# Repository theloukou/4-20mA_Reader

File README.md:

# 4-20mA_Reader
4-20mA to UART/I2C output

Atmega328/Arduino based device.  
Features selectable auto UART transmission, and I2C polling.

## DISCLAIMER  
Device has not been tested yet. Contact me if you make a board and are willing to test.

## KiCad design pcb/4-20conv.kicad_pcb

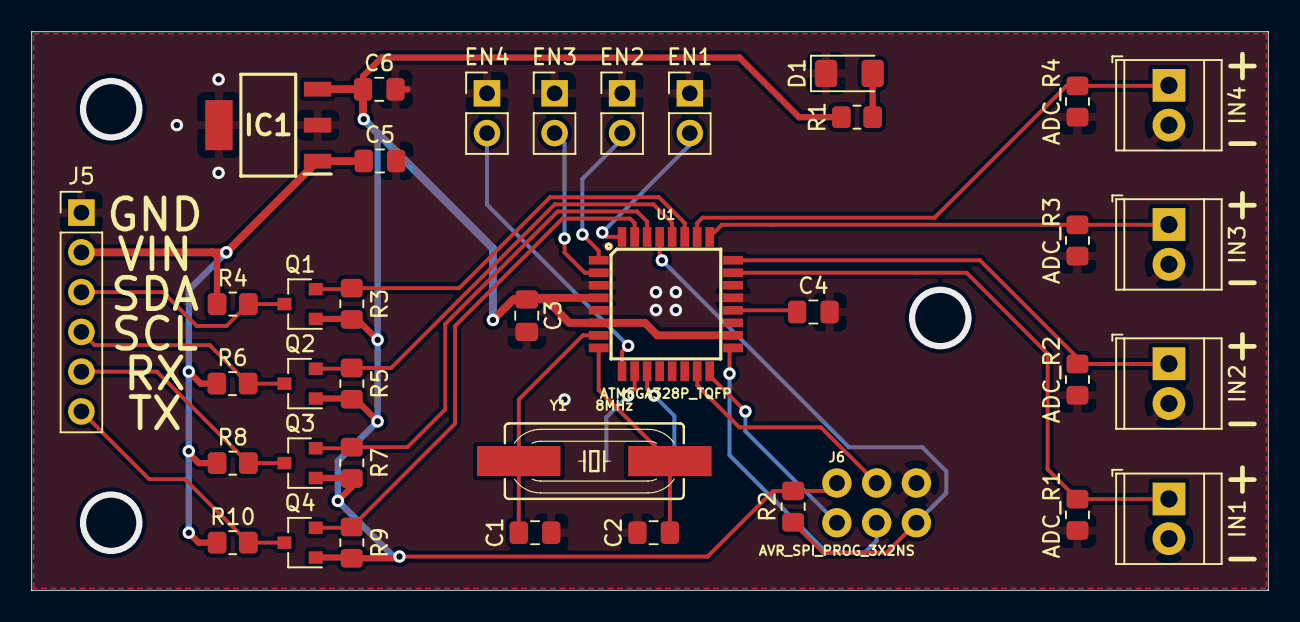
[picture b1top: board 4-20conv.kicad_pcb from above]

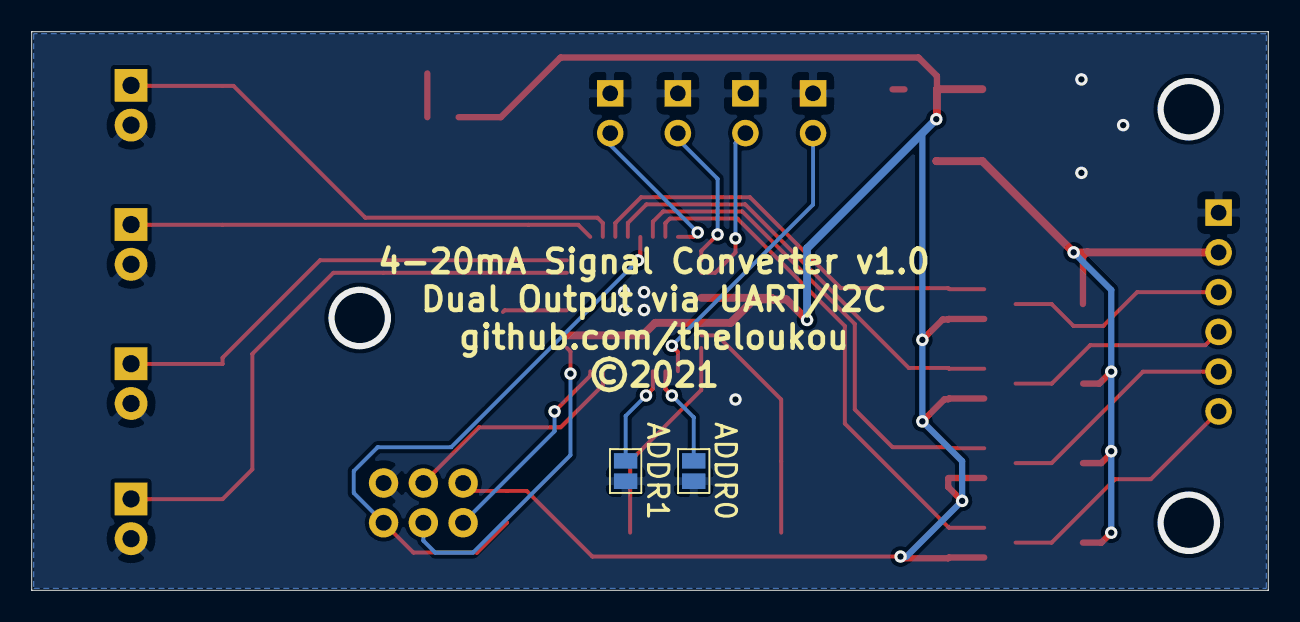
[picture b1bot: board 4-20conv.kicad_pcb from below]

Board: 2 copper layers, 79.0 x 35.7 mm, 40 parts (2 on the bottom side), 29 nets.

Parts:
ADC_R1, ADC_R2, ADC_R3, ADC_R4: 120R; R_0805_2012Metric_Pad1.20x1.40mm_HandSolder
ADDR0, ADDR1: SolderJumper_2_Open; SolderJumper-2_P1.3mm_Open_Pad1.0x1.5mm
C1, C2: 22p; C_0805_2012Metric_Pad1.18x1.45mm_HandSolder
C3, C4, C5: 100n; C_0805_2012Metric_Pad1.18x1.45mm_HandSolder
C6: 10u; C_0805_2012Metric_Pad1.18x1.45mm_HandSolder
D1: LED; LED_1206_3216Metric_Pad1.42x1.75mm_HandSolder
EN1, EN2, EN3, EN4: Jumper_2_Bridged; PinHeader_1x02_P2.54mm_Vertical
IC1: TPS7B8333QDCYRQ1; SOT230P700X180-4N
IN1, IN2, IN3, IN4: Screw_Term_01x02; TerminalBlock_TE_282834-2_1x02_P2.54mm_Horizontal
J5: Conn_01x06_Male; PinHeader_1x06_P2.54mm_Vertical
J6: AVR_SPI_PROG_3X2NS; 2X3-NS
Q1, Q2, Q3, Q4: BSS138; SOT-23
R1: 120R; R_0805_2012Metric_Pad1.20x1.40mm_HandSolder
R2, R3, R4, R5, R6, R7, R8, R9, R10: 10K; R_0805_2012Metric_Pad1.20x1.40mm_HandSolder
U1: ATMEGA328P_TQFP; TQFP32-08
Y1: 8MHz; HC49UP

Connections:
/ADDR0: ADDR0.1, U1.10
/ADDR1: ADDR1.1, U1.11
/AREF: C4.1, U1.20
/EN1: EN1.2, U1.32
/EN2: EN2.2, U1.1
/EN3: EN3.2, U1.2
/EN4: EN4.2, U1.9
/IN1: ADC_R1.2, IN1.1, U1.23
/IN2: ADC_R2.2, IN2.1, U1.24
/IN3: ADC_R3.2, IN3.1, U1.25
/IN4: ADC_R4.2, IN4.1, U1.26
/MISO: J6.1, U1.16
/MOSI: J6.4, U1.15
/RST: J6.5, R2.1, U1.29
/RX: J5.5, Q3.3, R8.2
/RX_MCU: Q3.2, R7.2, U1.30
/SCK: J6.3, U1.17
/SCL: J5.4, Q2.3, R6.2
/SCL_MCU: Q2.2, R5.2, U1.28
/SDA: J5.3, Q1.3, R4.2
/SDA_MCU: Q1.2, R3.2, U1.27
/TX: J5.6, Q4.3, R10.2
/TX_MCU: Q4.2, R9.2, U1.31
/XTAL1: C1.1, U1.7, Y1.2
/XTAL2: C2.1, U1.8, Y1.1
GND: ADC_R1.1, ADC_R2.1, ADC_R3.1, ADC_R4.1, ADDR0.2, ADDR1.2, C1.2, C2.2, C3.2, C4.2, C5.2, C6.2, D1.1, EN1.1, EN2.1, EN3.1, EN4.1, IC1.2, IC1.4, IN1.2, IN2.2, IN3.2, IN4.2, J5.1, J6.6, U1.3, U1.5, U1.21
unnamed: D1.2, R1.2
VCC: C3.1, C6.1, IC1.3, J6.2, Q1.1, Q2.1, Q3.1, Q4.1, R1.1, R2.2, R3.1, R5.1, R7.1, R9.1, U1.4, U1.6, U1.18
VIN: C5.1, IC1.1, J5.2, R4.1, R6.1, R8.1, R10.1

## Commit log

2021-09-29 1st commit

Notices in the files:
pcb/4-20conv.kicad_pcb:
©2021
